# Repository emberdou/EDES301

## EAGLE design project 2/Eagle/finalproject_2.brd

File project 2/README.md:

For this project I designed an Etch-a-sketch PCB. This was the given project as I do not think I could have fit the relay module on my board correctly given the specs. I used a PocketBeagle, USB port, buzzer, button, servo, potentiometer, LED and a display. I was able to get it to work sucesfully given the specifications.

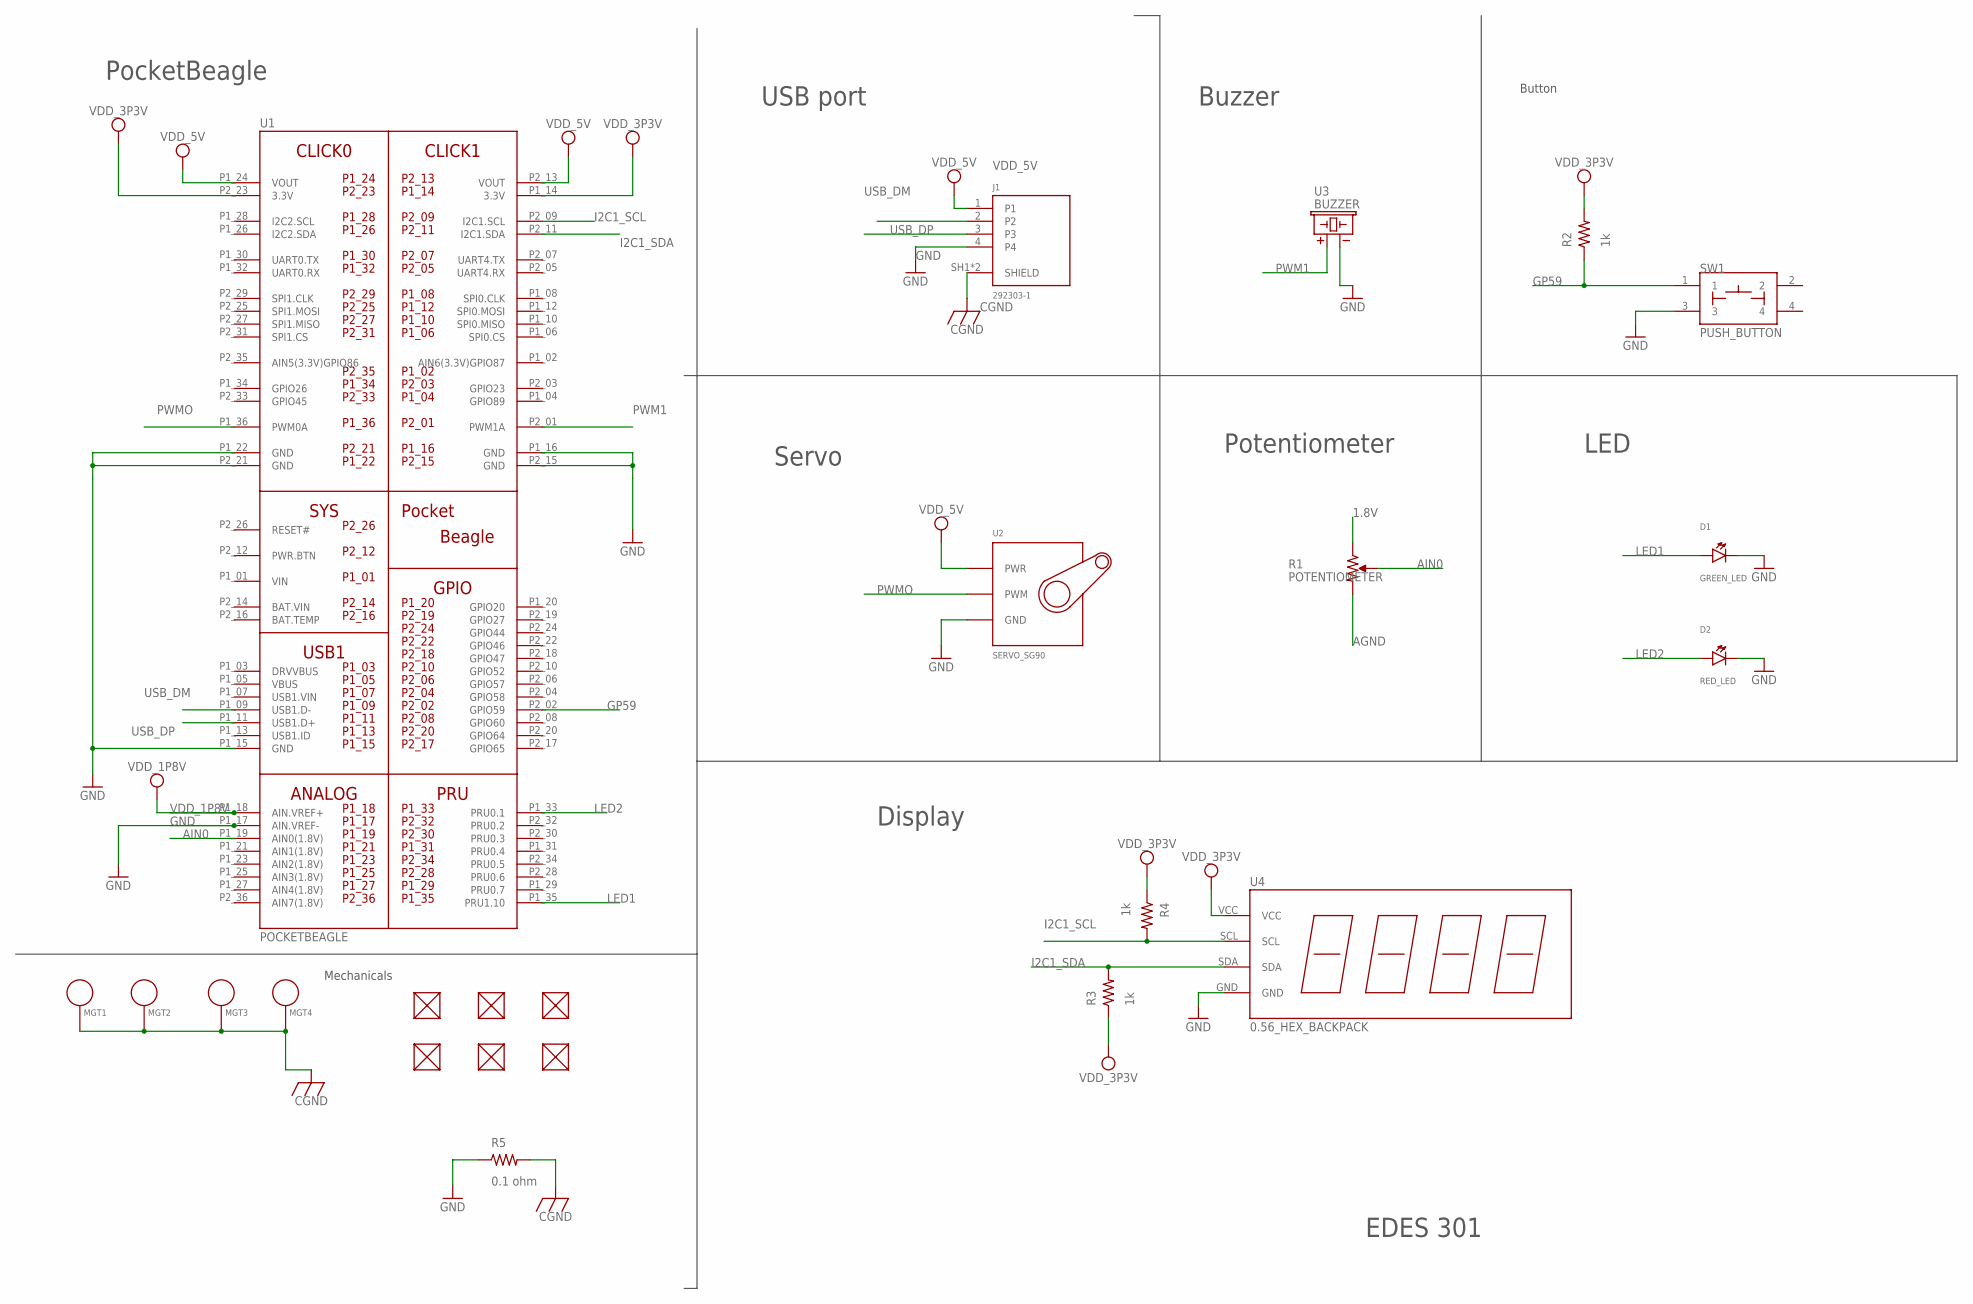
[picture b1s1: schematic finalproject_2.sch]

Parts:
D1: GREEN_LED; EIA-STD
D2: RED_LED; EIA-STD
FUD1, FUD2, FUD3, FUD4, FUD5, FUD6: FIDUCIAL; FIDUCIAL_40MIL
J1: 292303-1; TE_292303-1
MGT1, MGT2, MGT3, MGT4: MOUNTING_HOLE
R1: POTENTIOMETER; POT-PO90S
R2, R3, R4: 1k; R0402
R5: 0.1 ohm; R0805
SW1: PUSH_BUTTON; BUTTON_12.5MM
U1: POCKETBEAGLE
U2: SERVO_SG90; SERVO-X1
U3: BUZZER; BUZZER_6.5MM
U4: 0.56_HEX_BACKPACK

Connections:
1.8V: R1.CCW
AGND: R1.CW
AIN0: R1.S, U1.P1_19 (AIN0(1.8V))
BAT.VIN: U1.P2_14 (BAT.VIN)
CGND: J1.SH1 (SHIELD), J1.SH2 (SHIELD), MGT1.P$1, MGT2.P$1, MGT3.P$1, MGT4.P$1, R5.2
GND: D1.CATHODE, D2.CATHODE, J1.4, R5.1, SW1.3, U1.P1_15 (GND), U1.P1_16 (GND), U1.P1_17 (AIN.VREF-), U1.P1_22 (GND), U1.P2_15 (GND), U1.P2_21 (GND), U2.GND, U3.-, U4.GND
GP59: R2.1, SW1.1, U1.P2_02 (GPIO59)
I2C1_SCL: R4.2, U1.P2_09 (I2C1.SCL), U4.SCL
I2C1_SDA: R3.2, U1.P2_11 (I2C1.SDA), U4.SDA
LED1: D1.ANODE, U1.P1_35 (PRU1.10)
LED2: D2.ANODE, U1.P1_33 (PRU0.1)
PWM1: U1.P2_01 (PWM1A), U3.+
PWMO: U1.P1_36 (PWM0A), U2.SIG (PWM)
USB_DM: J1.2, U1.P1_09 (USB1.D-)
USB_DP: J1.3, U1.P1_11 (USB1.D+)
VDD_1P8V: U1.P1_18 (AIN.VREF+)
VDD_3P3V: R2.2, R3.1, R4.1, U1.P1_14 (3.3V), U1.P2_23 (3.3V), U4.VCC
VDD_5V: J1.1, U1.P1_24 (VOUT), U1.P2_13 (VOUT), U2.PWR
VIN: U1.P1_01 (VIN)

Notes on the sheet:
PocketBeagle
USB port
Servo
Buzzer
Display
Potentiometer
LED
Button
EDES 301
Mechanicals

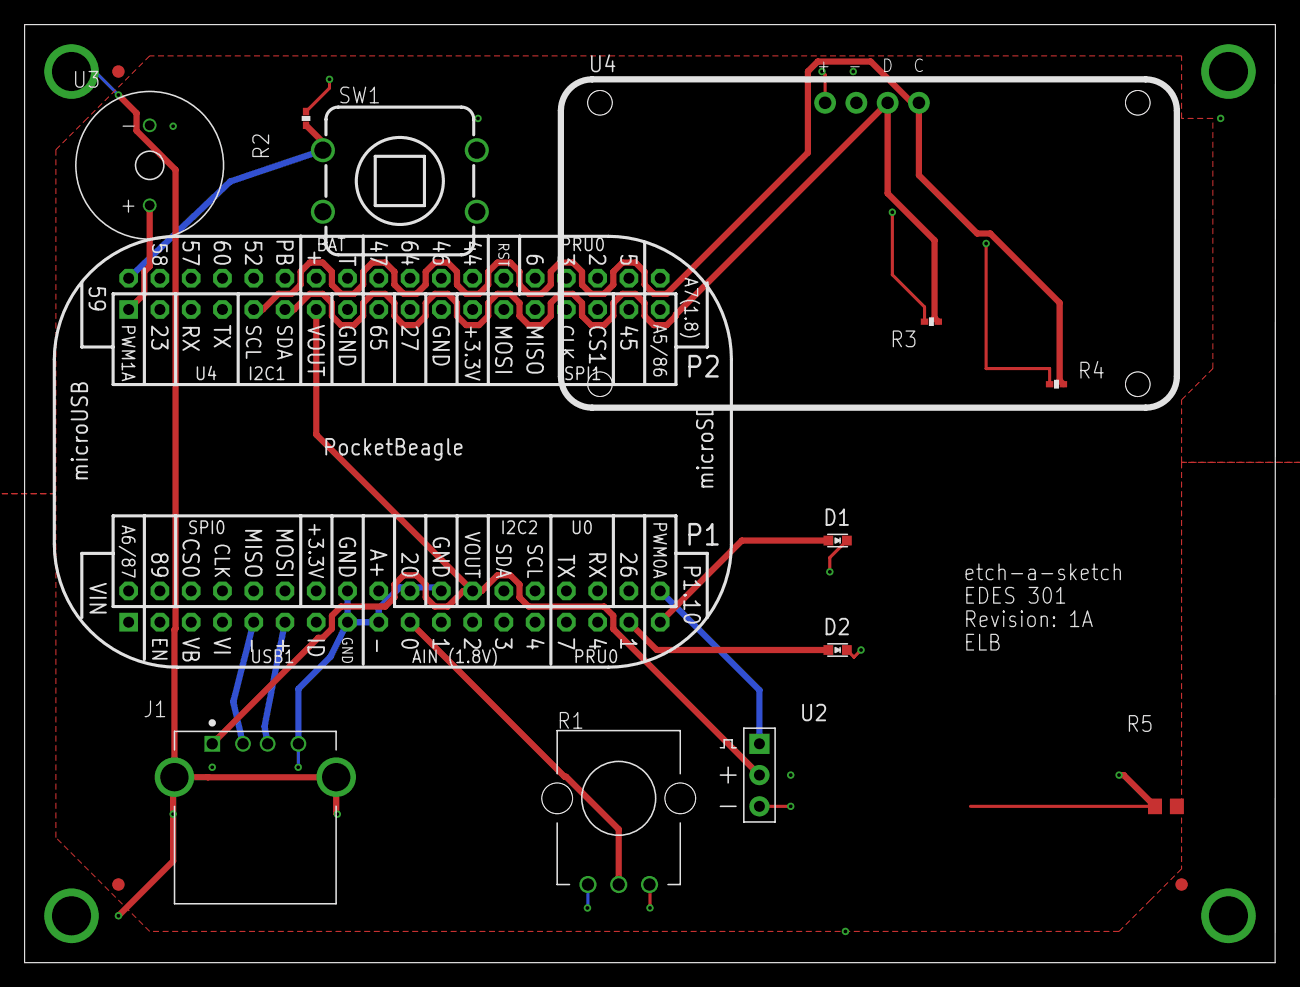
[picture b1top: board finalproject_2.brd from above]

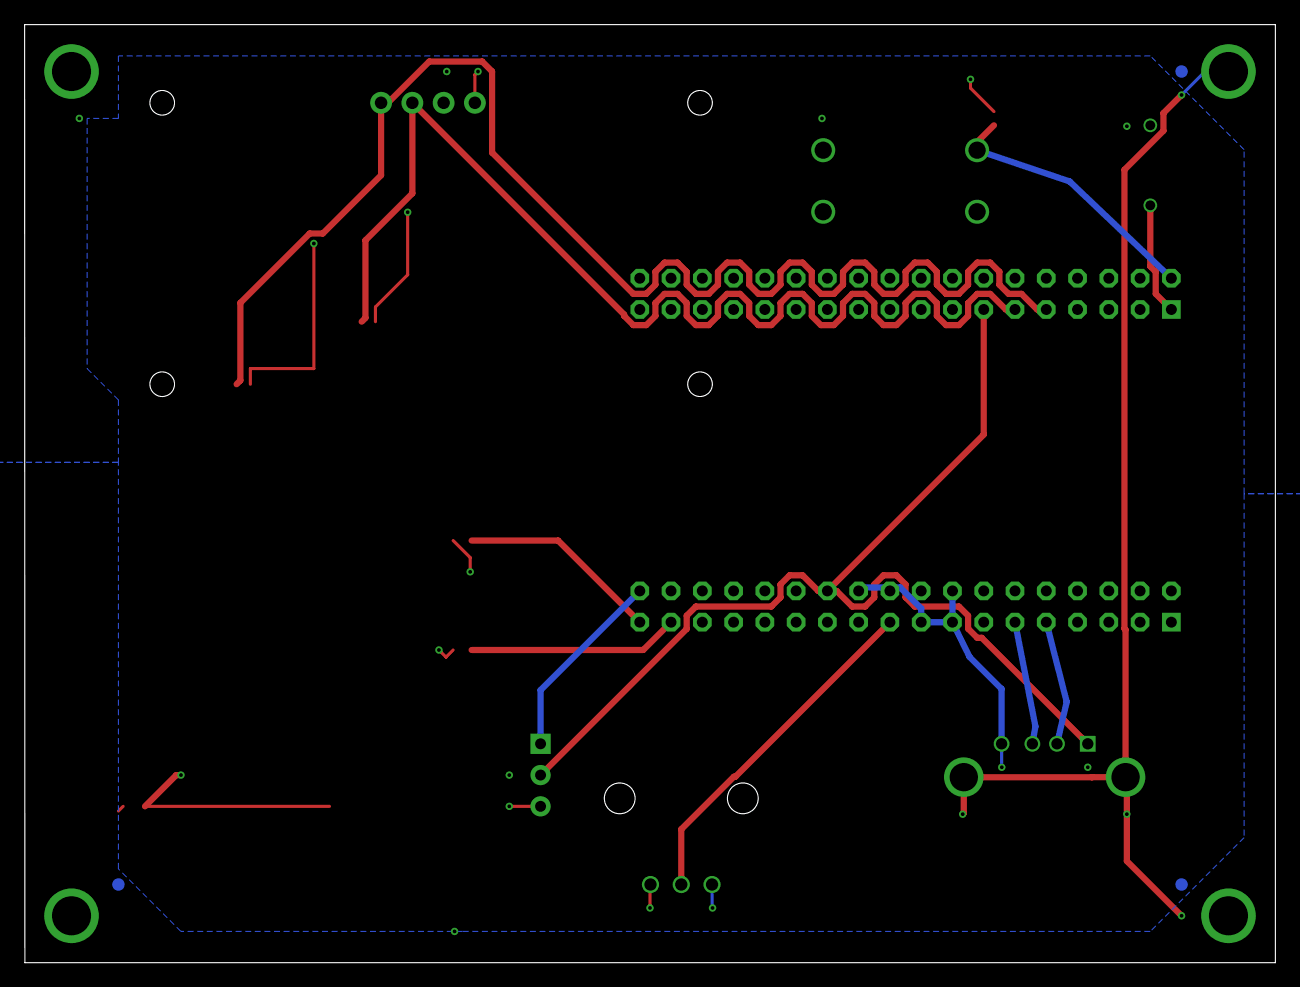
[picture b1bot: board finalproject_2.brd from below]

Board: 4 copper layers, 101.6 x 76.2 mm, 23 parts (3 on the bottom side), 14 nets.

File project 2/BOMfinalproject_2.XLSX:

BOMfinalproject_2
Qty | Value | Device | Package | Parts | Description | AVAILABILITY | CENTERLINE_PITCH | CHECK_PRICES | COMMENT | DESCRIPTION | EU_ROHS_COMPLIANCE | MF | MP | NUMBER_OF_POSITIONS | PACKAGE | PRICE | PRODUCT_TYPE | SNAPEDA_LINK
1 | 0.1 ohm | R_R0805 | R0805 | R5 | RESISTOR, American symbol
1 | 0.56_HEX_BACKPACK | 0.56_HEX_BACKPACK | 0.56_HEX_BACKPACK | U4 | 0.56 LED HEX Backback - Adafruit HT16K33 -"
3 | 1k | R_R0402 | R0402 | R2, R3, R4 | RESISTOR, American symbol
1 | 292303-1 | 292303-1 | TE_292303-1 | J1 | Check availability | In Stock | 2 mm[.078 in] | https://www.snapeda.com/parts/292303-1/TE+Connectivity+AMP+C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 | 292303-1 | Type A Standard USB Connector 4 Position Right Angle Mount 1 Port | TE Connecti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 | Compliant | TE Connectivity | 292303-1 | 4 | None | None | Connector | https://www.snapeda.com/parts/292303-1/TE+Connectivity+AMP+C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
1 | BUZZER | BUZZER | BUZZER_6.5MM | U3 | CEM-1203 Buzzer
6 | FIDUCIAL | FIDUCIAL | FIDUCIAL_40MIL | FUD1, FUD2, FUD3, FUD4, FUD5, FUD6
1 | GREEN_LED | LED | EIA-STD | D1 | EIA-STD LED, LTST-C191TBKT
4 | MOUNTING_HOLE | MOUNTING_HOLE | MOUNTING_HOLE | MGT1, MGT2, MGT3, MGT4 | Chassis Mounting Hole w/GND connection ability
1 | POCKETBEAGLE | POCKETBEAGLE | POCKETBEAGLE | U1
1 | POTENTIOMETER | POTENTIOMETER | POT-PO90S | R1 | Potentiometer - Examples:
1 | PUSH_BUTTON | PUSH_BUTTON | BUTTON_12.5MM | SW1
1 | RED_LED | LED | EIA-STD | D2 | EIA-STD LED, LTST-C191TBKT
1 | SERVO_SG90 | SERVO_SG90 | SERVO-X1 | U2

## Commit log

2025-02-18 commiting caluclator
2025-02-18 python
2025-02-18 commit message
2025-02-18 blink led
2025-04-08 adding files
2025-05-01 Create Project 2
